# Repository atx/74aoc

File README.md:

# 74aoc

A PCB solving [Advent of Code 2025 Day 1](https://adventofcode.com/2025/day/1) using 125 discrete 74-series logic chips synthesized via an automated Hardcaml -> nextpnr -> KiCad pipeline.

**Full writeup can be found on [my blog](https://atx.name/electronics/hardcaml-to-74-series-logic).**

Quick orientation guide:

 * `pcb/` contains the KiCad files. For reproducibility, those are "cooked" files that include the solution design loaded and routed (revert the appropriate commits for a fresh blank slate)
 * `hdl/` contains the Hardcaml source code and the Yosys+nextpnr orchestration. Some of the intermediate files are also commited for traceability. 
   * `dune exec ./test_solution.exe` runs the Hardcaml test bench
   * `dune exec ./build_solution.exe` outputs the Verilog source code from the Hardcaml solution (beware that this requires the preview version 0.18 of Hardcaml)
   * `top.v` includes the output of the previous step and wraps it to assign concrete IO pads to the signals
   * `./simulate.sh <preplace|pnr>` runs the Verilog testbench using Verilator, either on pre-placement Verilog or on the placement result from Nextpnr (using the appropriate cell models from nextpnr-generic)
 * The root directory contains several scripts that serve to translate results from `hdl` into `pcb`. Loading new design is done by running `translate_nets_to_kicad.py` and `load_luts_into_kicad.py`.
 * `controller/` this contains the bit banged driver for the board, to be executed on Raspberry Pi. Executed as `dune exec ./main.exe`, supports `--help`.

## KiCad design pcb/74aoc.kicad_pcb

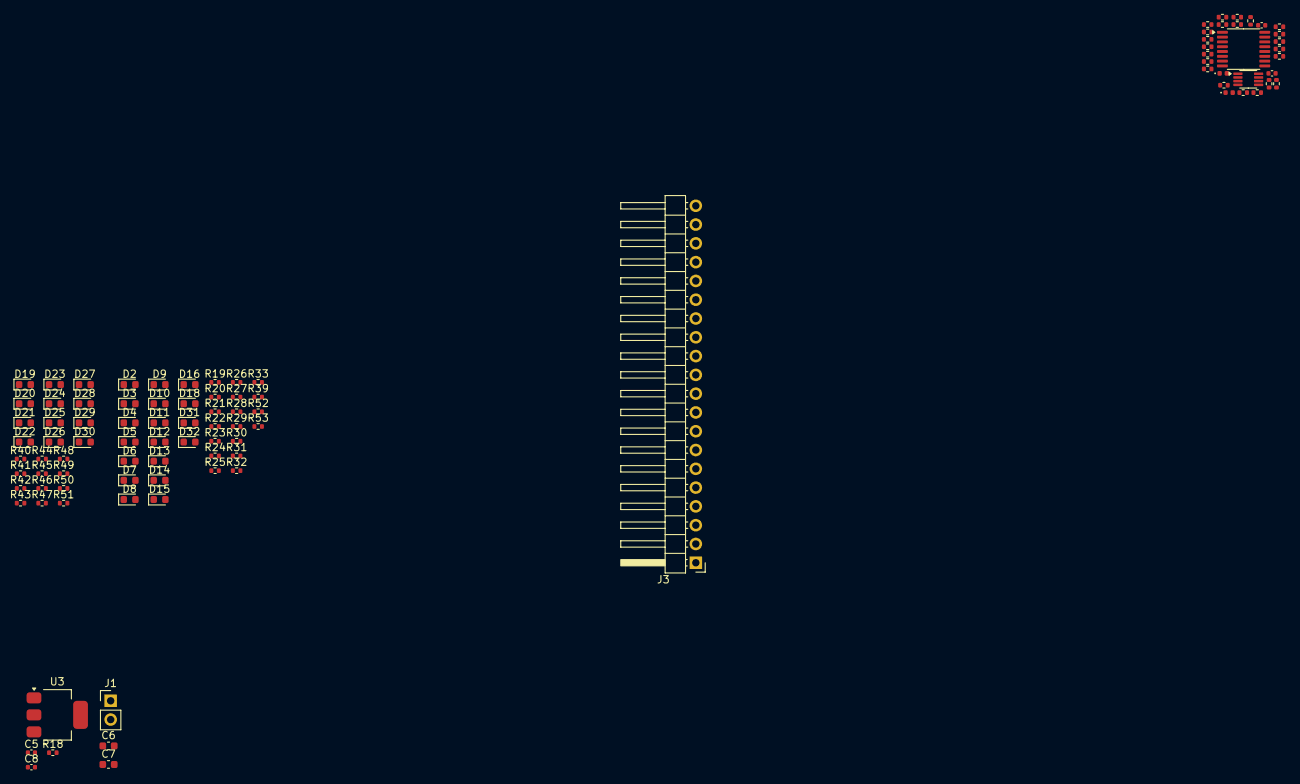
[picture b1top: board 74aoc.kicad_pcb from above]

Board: 2 copper layers, 96 parts (0 on the bottom side), 66 nets, no tracks yet.

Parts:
C1, C2, C5, C8: 100n; C_0402_1005Metric
C6, C7: 10u; C_0603_1608Metric
D1, D17: LED; LED_0402_1005Metric
D2, D3, D4, D5, D6, D7, D8, D9, D10, D11, D12, D13, D14, D15, D16, D18, D19, D20, D21, D22, D23, D24, D25, D26, D27, D28, D29, D30, D31, D32: LED; LED_0603_1608Metric
J1: Conn_01x02_Pin; PinHeader_1x02_P2.54mm_Vertical
J3: Conn_01x20_Pin; PinHeader_1x20_P2.54mm_Horizontal
R1, R2, R3, R4, R5, R6, R7, R8, R9, R10, R11, R12, R13, R14, R15, R16: 1k; R_0402_1005Metric
R17, R19, R20, R21, R22, R23, R24, R25, R26, R27, R28, R29, R30, R31, R32, R33, R34, R39, R40, R41, R42, R43, R44, R45, R46, R47, R48, R49, R50, R51, R52, R53: 10k; R_0402_1005Metric
R18: 1; R_0402_1005Metric
R35, R36: 0; R_0402_1005Metric
R37, R38: 100k; R_0402_1005Metric
U1: MC74HC151ADTR2G; TSSOP-16_4.4x5mm_P0.65mm
U2: SN74LVC1G74; VSSOP-8_2.3x2mm_P0.5mm
U3: AMS1117-3.3; SOT-223-3_TabPin2

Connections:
/CELL X0 Y0/~CLR: R17.1, R35.2, U2.6 (~CLR)
/CELL X0 Y0/~PRE: R34.1, R36.2, U2.7 (~PRE)
/Power/VIN: C7.1, C8.1, J1.1, U3.3 (VI)
CLK: J3.18, R52.1, U2.1 (C)
GND: C1.2, C2.2, C5.2, C6.2, C7.2, C8.2, D2.1 (K), D3.1 (K), D4.1 (K), D5.1 (K), D6.1 (K), D7.1 (K), D8.1 (K), D9.1 (K), D10.1 (K), D11.1 (K), D12.1 (K), D13.1 (K), D14.1 (K), D15.1 (K), D16.1 (K), D18.1 (K), D19.1 (K), D20.1 (K), D21.1 (K), D22.1 (K), D23.1 (K), D24.1 (K), D25.1 (K), D26.1 (K), D27.1 (K), D28.1 (K), D29.1 (K), D30.1 (K), D31.1 (K), D32.1 (K), J1.2, J3.20, R1.1, R4.1, R6.1, R8.1, R10.1, R12.1, R14.1, R16.1, R37.1, R38.1, U1.7 (~E), U1.8 (GND), U2.4 (GND), U3.1 (GND)
NRST: J3.19, R35.1, R36.1, R53.1
unnamed: C6.1, R18.1
unnamed: D1.1 (K), R37.2
unnamed: D2.2 (A), R19.2
unnamed: D3.2 (A), R20.2
unnamed: D4.2 (A), R21.2
unnamed: D5.2 (A), R22.2
unnamed: D6.2 (A), R23.2
unnamed: D7.2 (A), R24.2
unnamed: D8.2 (A), R25.2
unnamed: D9.2 (A), R26.2
unnamed: D10.2 (A), R27.2
unnamed: D11.2 (A), R28.2
unnamed: D12.2 (A), R29.2
unnamed: D13.2 (A), R30.2
unnamed: D14.2 (A), R31.2
unnamed: D15.2 (A), R32.2
unnamed: D16.2 (A), R33.2
unnamed: D17.1 (K), R38.2
unnamed: D18.2 (A), R39.2
unnamed: D19.2 (A), R40.2
unnamed: D20.2 (A), R41.2
unnamed: D21.2 (A), R42.2
unnamed: D22.2 (A), R43.2
unnamed: D23.2 (A), R44.2
unnamed: D24.2 (A), R45.2
unnamed: D25.2 (A), R46.2
unnamed: D26.2 (A), R47.2
unnamed: D27.2 (A), R48.2
unnamed: D28.2 (A), R49.2
unnamed: D29.2 (A), R50.2
unnamed: D30.2 (A), R51.2
unnamed: D31.2 (A), R52.2
unnamed: D32.2 (A), R53.2
unnamed: R1.2, R3.2, U1.4 (I0)
unnamed: R2.2, R4.2, U1.3 (I1)
unnamed: R5.2, R6.2, U1.2 (I2)
unnamed: R7.2, R8.2, U1.1 (I3)
unnamed: R9.2, R10.2, U1.15 (I4)
unnamed: R11.2, R12.2, U1.14 (I5)
unnamed: R13.2, R14.2, U1.13 (I6)
unnamed: R15.2, R16.2, U1.12 (I7)
VCC: C1.1, C2.1, C5.1, R2.1, R3.1, R5.1, R7.1, R9.1, R11.1, R13.1, R15.1, R17.2, R18.2, R34.2, U1.16 (VCC), U2.8 (VCC), U3.2 (VO)
W_IO_I0: J3.1, R19.1
W_IO_I1: J3.2, R20.1
W_IO_I2: J3.3, R21.1
W_IO_I3: J3.4, R22.1
W_IO_I4: J3.5, R23.1
W_IO_I5: J3.6, R24.1
W_IO_I6: J3.7, R25.1
W_IO_I7: J3.8, R26.1
W_IO_I8: J3.9, R27.1
W_IO_I9: J3.10, R28.1
W_IO_I10: J3.11, R29.1
W_IO_I11: J3.12, R30.1
W_IO_I12: J3.13, R31.1
W_IO_I13: J3.14, R32.1
W_IO_I14: J3.15, R33.1
W_IO_I15: J3.16, R39.1
W_X0_Y0_F: D1.2 (A), U1.5 (Z), U2.2 (D)
W_X0_Y0_Q: D17.2 (A), U2.5 (Q)

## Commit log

2025-11-29 Drag stuff from nexpnr/generic into this repository
    This is relatively pristine "blinky" example pulled straight from
    nextpnr. Will slowly be melded to something.
2025-11-30 Specify the architecture
    Scaffolding needs to be improved next. But, at this point, it will
    be possible to perform a feasibility study on each of the AoC problems
    to see if it is even possible to implement this...
2025-11-30 Some scaffolding cleanups
2025-12-01 Initial very rough solution
    Probably going to go for part 2 instead, should result in less resources
    hopefully.
2025-12-02 Initial version of the PCB
2025-12-02 Reduce the output width to 11 bits
    May possibly break, but saves a lot of cells...
2025-12-02 Add output LED array
2025-12-03 Remove IO shift registers
    Too complex
2025-12-03 More realistic IO cell placement
    Especially following the IO cell rethinking
2025-12-03 Create a script that duplicates the cell schematic instances
2025-12-03 Implement static IO cell assignments
2025-12-03 Remove the vestigial rst signal
2025-12-03 Route the basic elements + power + clk + rst network
2025-12-03 Enforce K = 3 more
    The Verilog was actually generated with K = 4 since we have not set it
    in nextpnr. But, it has no practical impact since the architecture does
    not provide any wires into the fourth input...
2025-12-04 Slightly more spacious spacing of the output LEDs
2025-12-04 Add a script to translate nextpnr nets into KiCad
2025-12-05 Initialize all DFFs to 0
    Oops did not realize that nextpnr can only do 1 anyway...
2025-12-05 Initial Hardcaml version
2025-12-05 Fix and finalize the KiCad loading pipeline
2025-12-05 Restructure a bit in preparation for Hardcaml testbench
2025-12-05 Add an actual fr Hardcaml testbench
2025-12-05 Slightly more canonical Hardcaml
    Not by a lot...
2025-12-05 Drop unused files
2025-12-06 PCB prettification
2025-12-06 Some final PCB touches
2025-12-06 Fix off by one when translating LUT input indices
2025-12-06 Tag unused Muxes/DFFs for not-populating
2025-12-06 Wire unused inputs to ground
    Should be done according to the mux datasheet...
2025-12-06 Add LCSC codes to everything that did not have them yet
2025-12-07 Bake everything into the PCB (+ commit the intermediates)
    This is mostly for traceability reproducibility reasons.
    In practice, the best way to bake a different design would be to branch
    off just before this commit
2025-12-07 Add JLCPCB_CORRECTION
2025-12-07 Fix not-updated tests
    Borked in 6073ab606cf0a1cc73d89a0afe652551f7a4288b and forgot to re-run
2025-12-20 Initial version of the controller
2025-12-24 Simple visualization script
2025-12-29 Add no sleep mode to the controller
    Still pretty slow, more speed needed
2025-12-29 Use Raspberry Pi specific GPIO library
    This allows faster bit banging as we do not have to do an ioctl for
    every GPIO change...
2025-12-31 Add a license
2026-01-01 Add README
2026-01-02 Add a nice title image
2026-01-05 Remove some dead code
